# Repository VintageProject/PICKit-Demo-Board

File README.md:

# PICKit-Demo-Board
Microcontroller demo board based of the old PICKit demo board

Feel free to use the design.

As usual, I can't offer any guarantees or warranties. The design is presented as-is.
If you find errors, feel free to let me know, or to fork the repo.

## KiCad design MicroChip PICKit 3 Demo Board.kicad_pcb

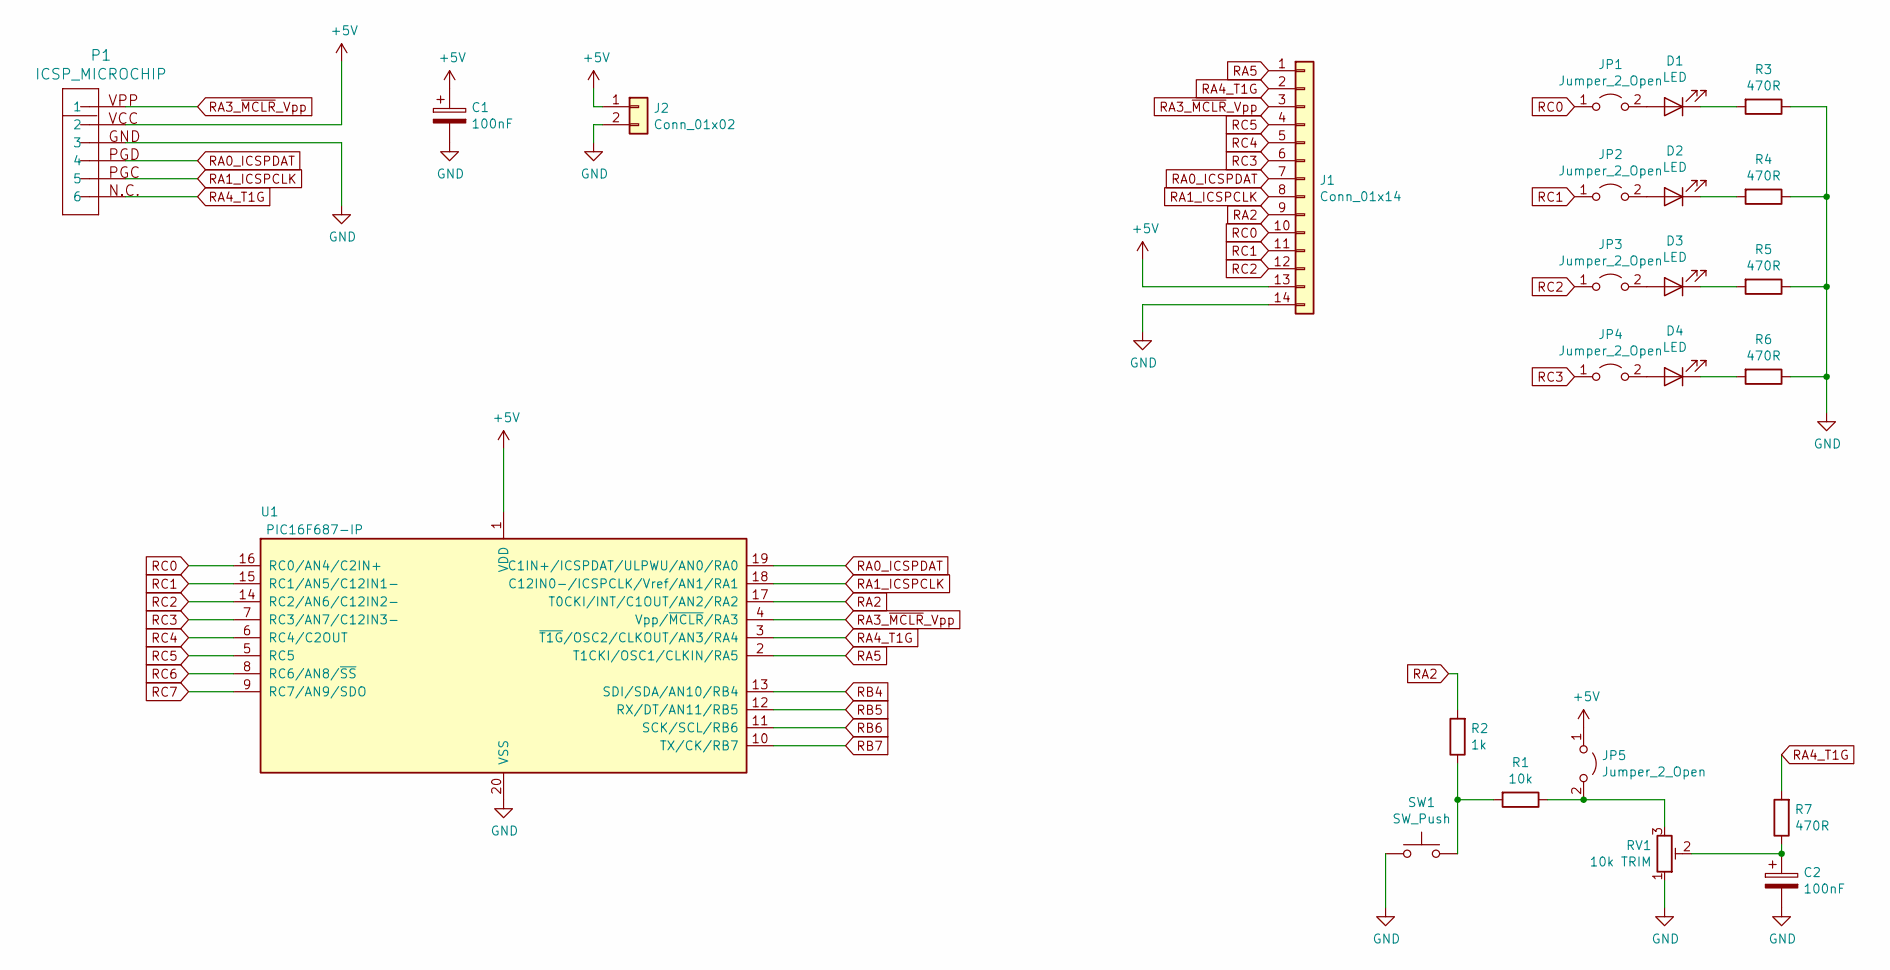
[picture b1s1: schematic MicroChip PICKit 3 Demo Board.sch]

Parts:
C1, C2: 100nF; CP_Axial_L11.0mm_D5.0mm_P18.00mm_Horizontal
D1, D2, D3, D4: LED; LED_D5.0mm
J1: Conn_01x14; PinHeader_1x14_P2.54mm_Vertical
J2: Conn_01x02; PinHeader_1x02_P2.54mm_Vertical
JP1, JP2, JP3, JP4, JP5: Jumper_2_Open; PinHeader_1x02_P2.54mm_Vertical
P1: ICSP_MICROCHIP; PinHeader_1x06_P2.54mm_Horizontal
R1: 10k; R_Axial_DIN0309_L9.0mm_D3.2mm_P12.70mm_Horizontal
R2: 1k; R_Axial_DIN0309_L9.0mm_D3.2mm_P12.70mm_Horizontal
R3, R4, R5, R6, R7: 470R; R_Axial_DIN0309_L9.0mm_D3.2mm_P12.70mm_Horizontal
RV1: 10k TRIM; Potentiometer_Bourns_3266P_Horizontal
SW1: SW_Push; SW_PUSH_6mm_H5mm
U1: PIC16F687-IP; DIP-20_W7.62mm_LongPads

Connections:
+5V: C1.1, J1.13, J2.1, JP5.1 (A), P1.2, U1.1 (VDD); also elsewhere on the board
GND: C1.2, C2.2, J1.14, J2.2, P1.3, R3.1, R4.1, R5.1, R6.1, RV1.1, SW1.1, U1.20 (VSS); also elsewhere on the board
unnamed: C2.1, R7.1, RV1.2
unnamed: D1.1 (K), R3.2
unnamed: D1.2 (A), JP1.2 (B)
unnamed: D2.1 (K), R4.2
unnamed: D2.2 (A), JP2.2 (B)
unnamed: D3.1 (K), R5.2
unnamed: D3.2 (A), JP3.2 (B)
unnamed: D4.1 (K), R6.2
unnamed: D4.2 (A), JP4.2 (B)
unnamed: JP5.2 (B), R1.1, RV1.3
unnamed: R1.2, R2.1, SW1.2
RA0_ICSPDAT: J1.7, P1.4, U1.19 (C1IN+/ICSPDAT/ULPWU/AN0/RA0); also elsewhere on the board
RA1_ICSPCLK: J1.8, P1.5, U1.18 (C12IN0-/ICSPCLK/Vref/AN1/RA1); also elsewhere on the board
RA2: J1.9, R2.2, U1.17 (T0CKI/INT/C1OUT/AN2/RA2)
RA3_~MCLR~_Vpp: J1.3, P1.1, U1.4 (Vpp/~MCLR~/RA3); also elsewhere on the board
RA4_T1G: J1.2, P1.6, R7.2, U1.3 (~T1G~/OSC2/CLKOUT/AN3/RA4); also elsewhere on the board
RA5: J1.1, U1.2 (T1CKI/OSC1/CLKIN/RA5)
RB4: U1.13 (SDI/SDA/AN10/RB4)
RB5: U1.12 (RX/DT/AN11/RB5)
RB6: U1.11 (SCK/SCL/RB6)
RB7: U1.10 (TX/CK/RB7)
RC0: J1.10, JP1.1 (A), U1.16 (RC0/AN4/C2IN+)
RC1: J1.11, JP2.1 (A), U1.15 (RC1/AN5/C12IN1-)
RC2: J1.12, JP3.1 (A), U1.14 (RC2/AN6/C12IN2-)
RC3: J1.6, JP4.1 (A), U1.7 (RC3/AN7/C12IN3-)
RC4: J1.5, U1.6 (RC4/C2OUT)
RC5: J1.4, U1.5 (RC5)
RC6: U1.8 (RC6/AN8/~SS~)
RC7: U1.9 (RC7/AN9/SDO)

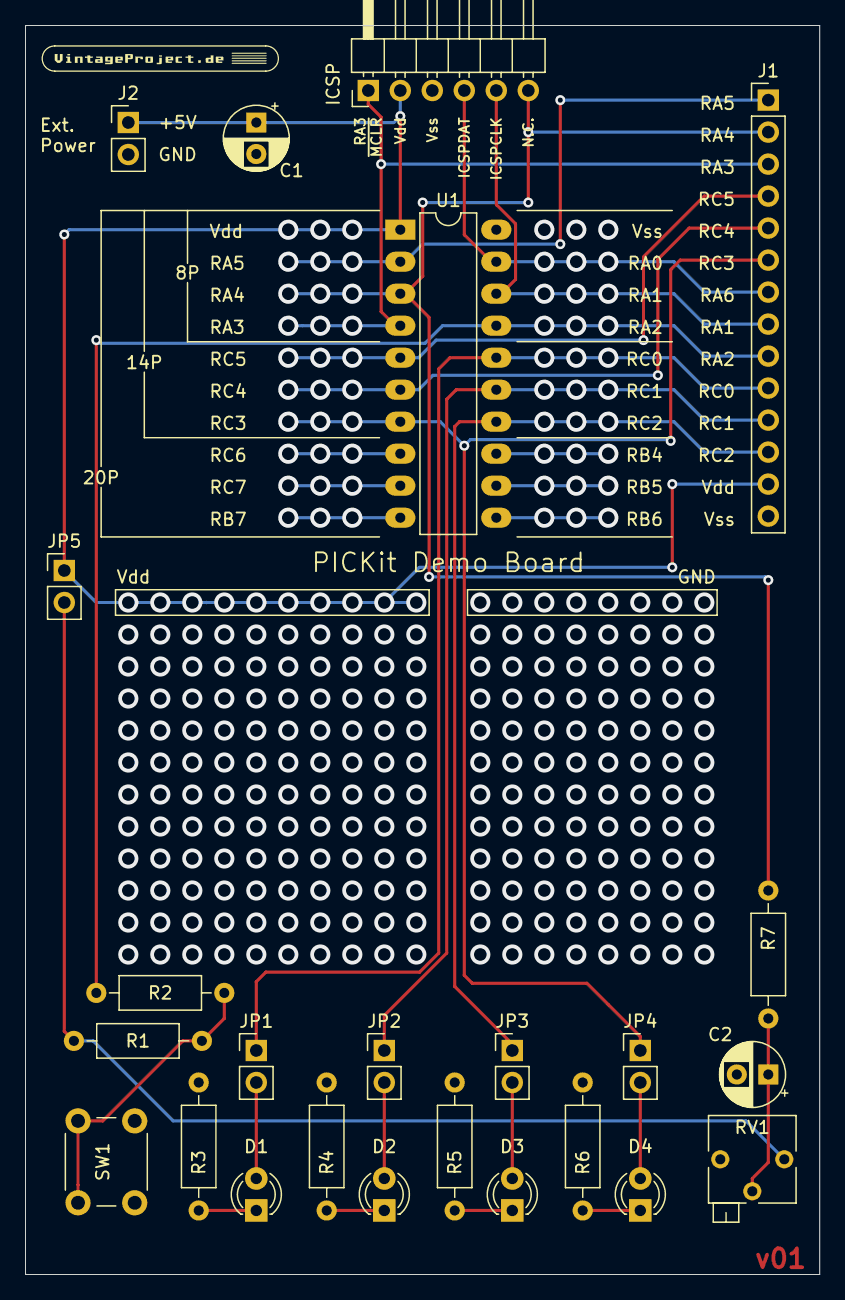
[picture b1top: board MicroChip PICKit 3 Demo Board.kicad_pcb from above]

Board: 2 copper layers, 63.0 x 99.1 mm, 24 parts (0 on the bottom side), 25 nets.

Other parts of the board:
ICSP: ICSP_MICROCHIP; PinHeader_1x06_P2.54mm_Horizontal

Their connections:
+5V: ICSP.2; also elsewhere on the board
GND: ICSP.3; also elsewhere on the board
RA0_ICSPDAT: ICSP.4; also elsewhere on the board
RA1_ICSPCLK: ICSP.5; also elsewhere on the board
RA3_~MCLR~_Vpp: ICSP.1; also elsewhere on the board
RA4_T1G: ICSP.6; also elsewhere on the board

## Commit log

2020-05-29 Initial upload
